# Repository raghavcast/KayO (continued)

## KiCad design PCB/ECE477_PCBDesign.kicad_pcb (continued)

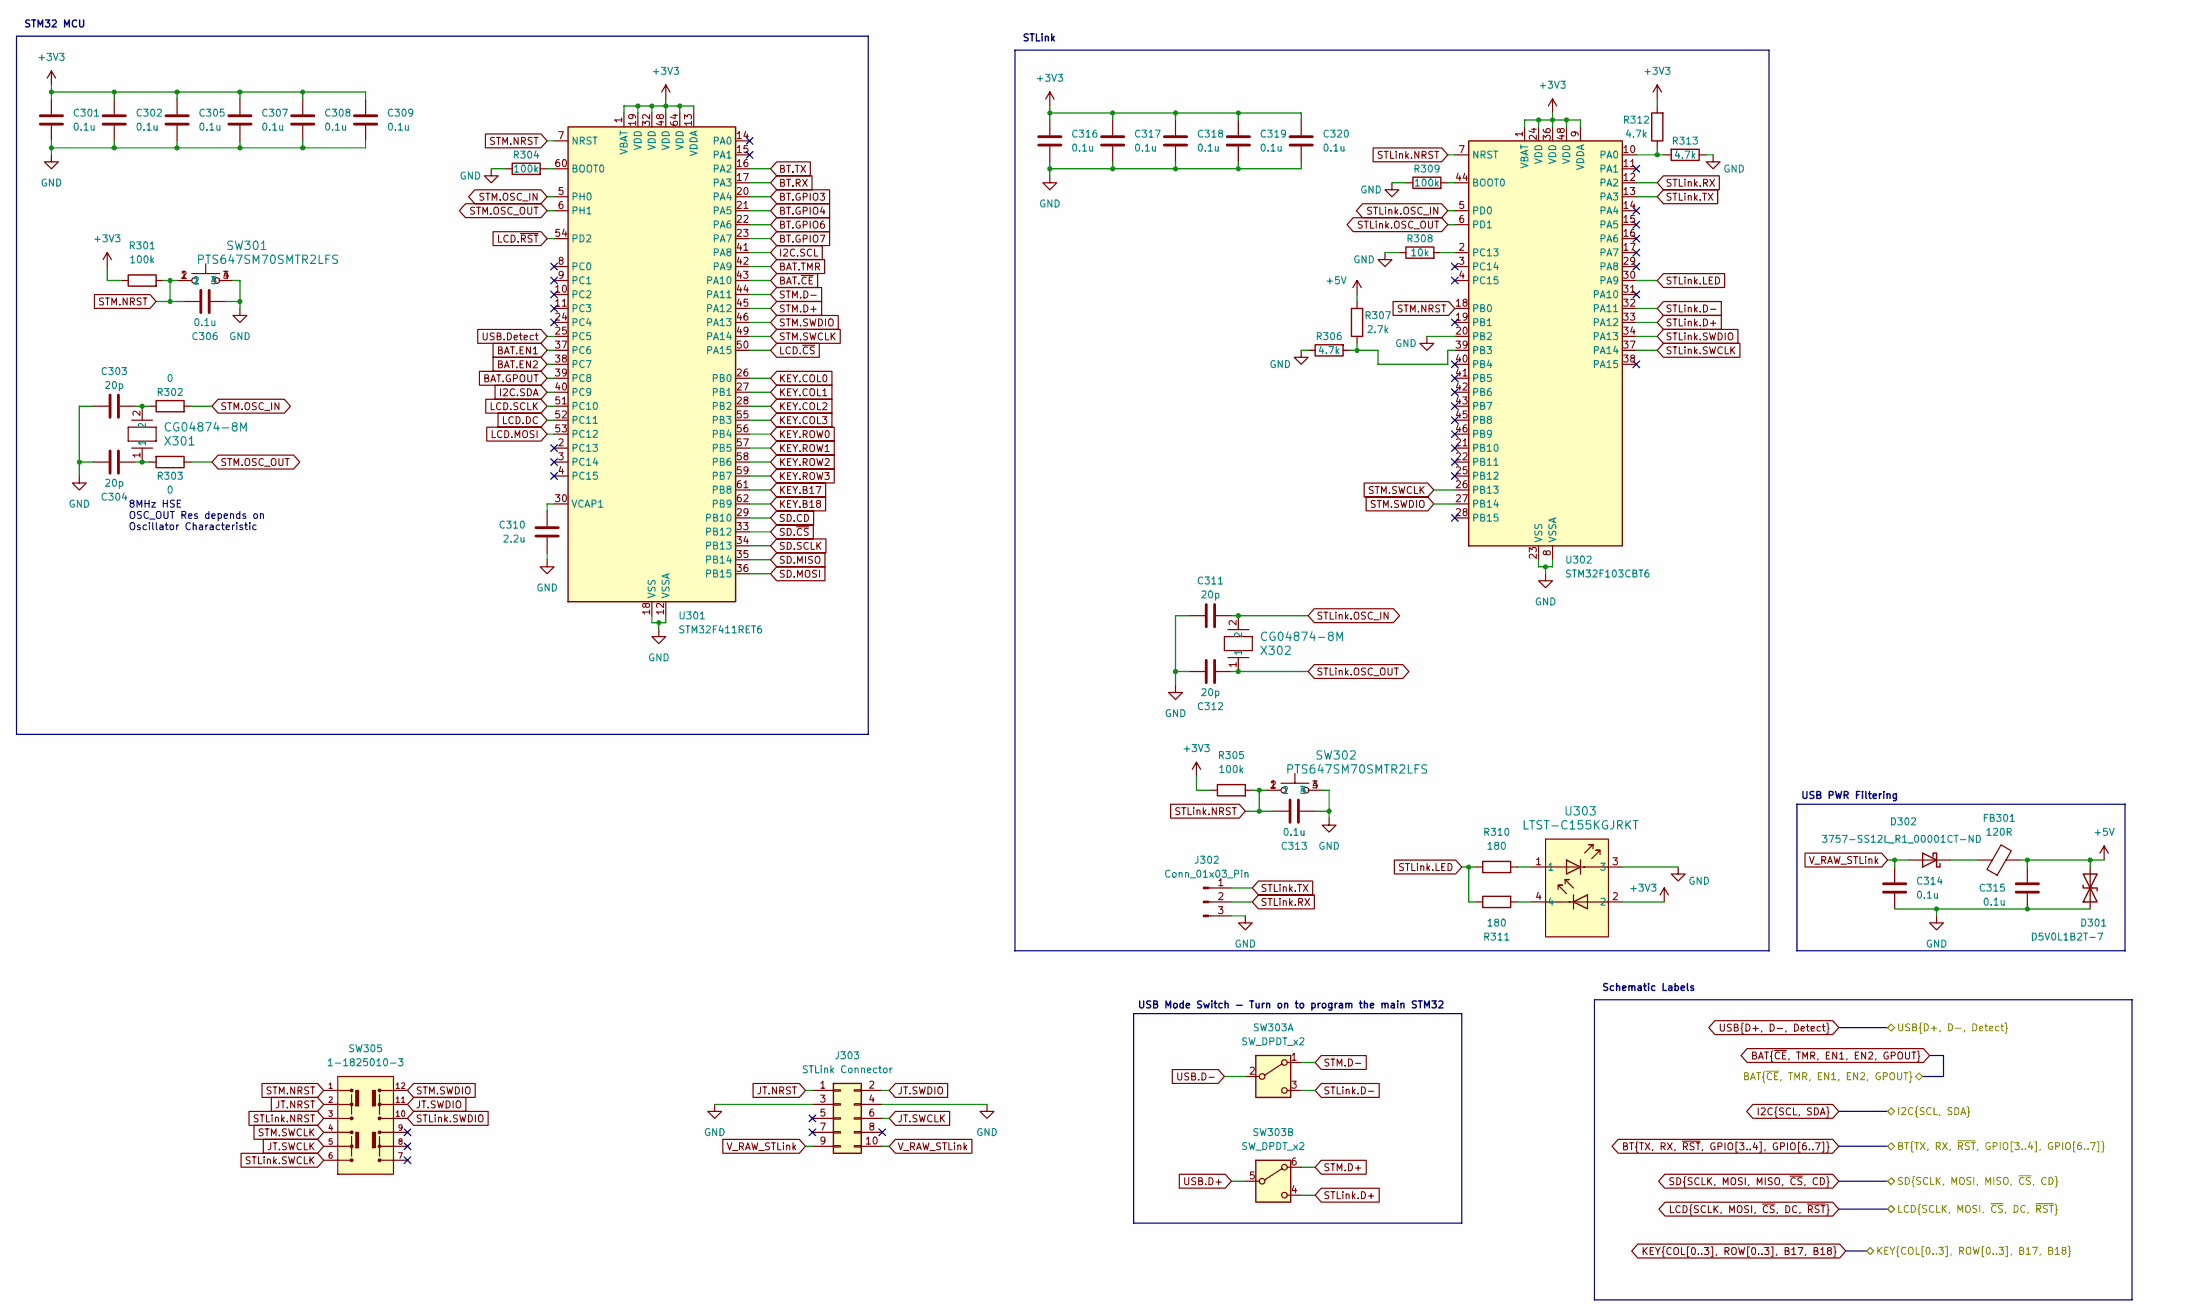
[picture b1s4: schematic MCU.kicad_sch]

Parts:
C301, C302, C305, C306, C307, C308, C309, C313, C316, C317, C318, C319, C320: 0.1u; C_0603_1608Metric_Pad1.08x0.95mm_HandSolder; Mfg. Part # GRM033R61A104ME15D; DigiKey Part 490-5405-1-ND
C303, C304, C311, C312: 20p; C_0603_1608Metric_Pad1.08x0.95mm_HandSolder; Mfg. Part # CC0603JRNPO9BN200; DigiKey Part 311-1424-1-ND
C310: 2.2u; C_0603_1608Metric_Pad1.08x0.95mm_HandSolder; Mfg. Part # GRM188R61E225KA12D; DigiKey Part 490-10731-1-ND
C314, C315: 0.1u; C_0603_1608Metric_Pad1.08x0.95mm_HandSolder; Mfg. Part # GRM033R61A104ME15D; LCSC C1525
D301: D5V0L1B2T-7; D_SOD-523; Mfg. Part # D5V0L1B2T-7; LCSC C508181
D302: 3757-SS12L_R1_00001CT-ND; D_SMA; Mfg. Part # SS12L_R1_00001; LCSC C36975
FB301: 120R; L_0603_1608Metric; Mfg. Part # BLM18BD121SH1D; LCSC C279682
J302: Conn_01x03_Pin; PinHeader_1x03_P2.54mm_Vertical
J303: STLink Connector; CONN10_302-S101_OST; Mfg. Part # 302-S101; DigiKey Part ED1543-ND
R301, R304, R305, R309: 100k; R_0603_1608Metric_Pad0.98x0.95mm_HandSolder; Mfg. Part # RC0603FR-07100KL; DigiKey Part 311-100KHRCT-ND
R302, R303: 0; R_0603_1608Metric_Pad0.98x0.95mm_HandSolder; Mfg. Part # RC0603JR-070RL; DigiKey Part 311-0.0GRCT-ND
R306, R312, R313: 4.7k; R_0603_1608Metric_Pad0.98x0.95mm_HandSolder; Mfg. Part # RC0603FR-074K7L; DigiKey Part 311-4.70KHRCT-ND
R307: 2.7k; R_0603_1608Metric_Pad0.98x0.95mm_HandSolder; Mfg. Part # RMCF0603FT2K70; DigiKey Part RMCF0603FT2K70CT-ND
R308: 10k; R_0603_1608Metric_Pad0.98x0.95mm_HandSolder; Mfg. Part # RC0603JR-0710KL; DigiKey Part 311-10KGRCT-ND
R310, R311: 180; R_0603_1608Metric_Pad0.98x0.95mm_HandSolder; Mfg. Part # RC0603FR-13180RL; DigiKey Part 13-RC0603FR-13180RLCT-ND
SW301, SW302: PTS647SM70SMTR2LFS; PTS647SM70SMTR2LFS_CNK; Mfg. Part # PTS 647 SM70 SMTR2 LFS; DigiKey Part PTS647SM70SMTR2LFSCT-ND
SW303: SW_DPDT_x2; SW_JS202011SCQN; Mfg. Part # JS202011SCQN; DigiKey Part 401-2002-1-ND
SW305: 1-1825010-3; SW_1-1825010-3; Mfg. Part # 1-1825010-3
U301: STM32F411RET6; LQFP-64_10x10mm_P0.5mm; Mfg. Part # STM32F411RET6; DigiKey Part 497-14909-ND
U302: STM32F103CBT6; LQFP-48_7x7mm_P0.5mm; Mfg. Part # STM32F103CBT6; DigiKey Part 497-6288-ND
U303: LTST-C155KGJRKT; SON4_LTST-C155KGJRKT_LTO; Mfg. Part # LTST-C155KGJRKT; DigiKey Part 160-1409-1-ND
X301, X302: CG04874-8M; XTAL_CG04874_NDK; Mfg. Part # CG04874-8M; DigiKey Part 644-CG04874-8MCT-ND

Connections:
+3V3: C301.1, C302.1, C305.1, C307.1, C308.1, C309.1, C316.1, C317.1, C318.1, C319.1, C320.1, R301.1, R305.1, R312.2, U301.1 (VBAT), U301.13 (VDDA), U301.19 (VDD), U301.32 (VDD), U301.48 (VDD), U301.64 (VDD), U302.1 (VBAT), U302.9 (VDDA), U302.24 (VDD), U302.36 (VDD), U302.48 (VDD), U303.2; also elsewhere on the board
+5V: C315.1, D301.2 (A2), FB301.2, R307.2; also elsewhere on the board
BAT.EN1: U301.37 (PC6); also elsewhere on the board
BAT.EN2: U301.38 (PC7); also elsewhere on the board
BAT.GPOUT: U301.39 (PC8); also elsewhere on the board
BAT.TMR: U301.42 (PA9); also elsewhere on the board
BAT.~CE: U301.43 (PA10); also elsewhere on the board
BT.GPIO3: U301.20 (PA4); also elsewhere on the board
BT.GPIO4: U301.21 (PA5); also elsewhere on the board
BT.GPIO6: U301.22 (PA6); also elsewhere on the board
BT.GPIO7: U301.23 (PA7); also elsewhere on the board
BT.RX: U301.17 (PA3); also elsewhere on the board
BT.TX: U301.16 (PA2); also elsewhere on the board
GND: C301.2, C302.2, C303.1, C304.1, C305.2, C306.1, C307.2, C308.2, C309.2, C310.2, C311.1, C312.1, C313.1, C314.2, C315.2, C316.2, C317.2, C318.2, C319.2, C320.2, D301.1 (A1), J302.3, J303.3, J303.4, R304.1, R306.1, R308.1, R309.1, R313.1, SW301.3, SW301.4, SW302.3, SW302.4, U301.12 (VSSA), U301.18 (VSS), U301.31 (VSS), U301.47 (VSS), U301.63 (VSS), U302.8 (VSSA), U302.20 (PB2), U302.23 (VSS), U302.35 (VSS), U302.47 (VSS), U303.3; also elsewhere on the board
I2C.SCL: U301.41 (PA8); also elsewhere on the board
I2C.SDA: U301.40 (PC9); also elsewhere on the board
JT.NRST: J303.1, SW305.2
JT.SWCLK: J303.6, SW305.5
JT.SWDIO: J303.2, SW305.11
KEY.B17: U301.61 (PB8); also elsewhere on the board
KEY.B18: U301.62 (PB9); also elsewhere on the board
KEY.COL0: U301.26 (PB0); also elsewhere on the board
KEY.COL1: U301.27 (PB1); also elsewhere on the board
KEY.COL2: U301.28 (PB2); also elsewhere on the board
KEY.COL3: U301.55 (PB3); also elsewhere on the board
KEY.ROW0: U301.56 (PB4); also elsewhere on the board
KEY.ROW1: U301.57 (PB5); also elsewhere on the board
KEY.ROW2: U301.58 (PB6); also elsewhere on the board
KEY.ROW3: U301.59 (PB7); also elsewhere on the board
LCD.DC: U301.52 (PC11); also elsewhere on the board
LCD.MOSI: U301.53 (PC12); also elsewhere on the board
LCD.SCLK: U301.51 (PC10); also elsewhere on the board
LCD.~CS: U301.50 (PA15); also elsewhere on the board
LCD.~RST: U301.54 (PD2); also elsewhere on the board
unnamed: C303.2, R302.1, X301.2
unnamed: C304.2, R303.2, X301.1
unnamed: D302.1 (K), FB301.1
unnamed: R310.2, U303.1
unnamed: R311.2, U303.4
unnamed: R304.2, U301.60 (BOOT0)
unnamed: C310.1, U301.30 (VCAP1)
unnamed: R309.2, U302.44 (BOOT0)
unnamed: R312.1, R313.2, U302.10 (PA0)
unnamed: R306.2, R307.1, U302.39 (PB3)
unnamed: R308.2, U302.2 (PC13)
SD.CD: U301.29 (PB10); also elsewhere on the board
SD.MISO: U301.35 (PB14); also elsewhere on the board
SD.MOSI: U301.36 (PB15); also elsewhere on the board
SD.SCLK: U301.34 (PB13); also elsewhere on the board
SD.~CS: U301.33 (PB12); also elsewhere on the board
STLink.D+: SW303.4 (C), U302.33 (PA12)
STLink.D-: SW303.3 (C), U302.32 (PA11)
STLink.LED: R310.1, R311.1, U302.30 (PA9)
STLink.NRST: C313.2, R305.2, SW302.1, SW302.2, SW305.3, U302.7 (NRST)
STLink.OSC_IN: C311.2, U302.5 (PD0), X302.2
STLink.OSC_OUT: C312.2, U302.6 (PD1), X302.1
STLink.RX: J302.2, U302.12 (PA2)
STLink.SWCLK: SW305.6, U302.37 (PA14)
STLink.SWDIO: SW305.10, U302.34 (PA13)
STLink.TX: J302.1, U302.13 (PA3)
STM.D+: SW303.6 (A), U301.45 (PA12)
STM.D-: SW303.1 (A), U301.44 (PA11)
STM.NRST: C306.2, R301.2, SW301.1, SW301.2, SW305.1, U301.7 (NRST), U302.18 (PB0)
STM.OSC_IN: R302.2, U301.5 (PH0)
STM.OSC_OUT: R303.1, U301.6 (PH1)
STM.SWCLK: SW305.4, U301.49 (PA14), U302.26 (PB13)
STM.SWDIO: SW305.12, U301.46 (PA13), U302.27 (PB14)
USB.D+: SW303.5 (B); also elsewhere on the board
USB.D-: SW303.2 (B); also elsewhere on the board
USB.Detect: U301.25 (PC5); also elsewhere on the board
V_RAW_STLink: C314.1, D302.2 (A), J303.9, J303.10

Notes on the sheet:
STM32 MCU
Schematic Labels
STLink
USB Mode Switch - Turn on to program the main STM32
8MHz HSE OSC_OUT Res depends on Oscillator Characteristic
USB PWR Filtering

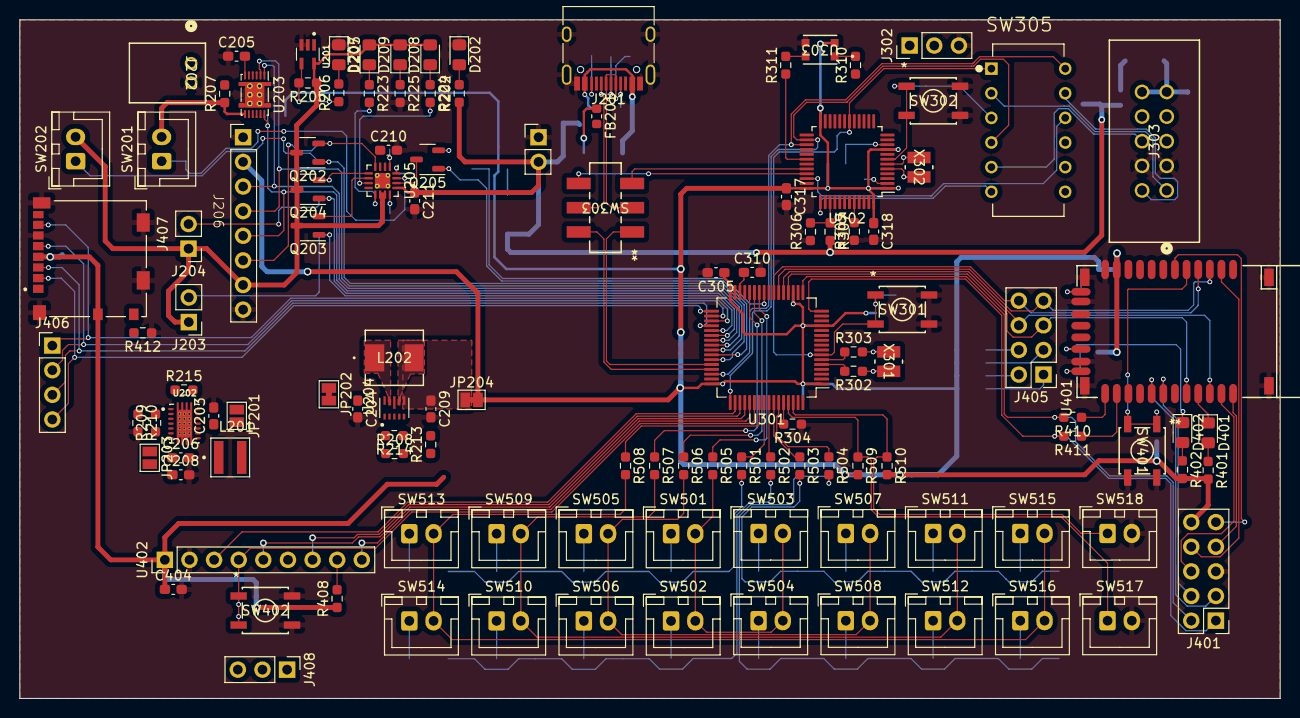
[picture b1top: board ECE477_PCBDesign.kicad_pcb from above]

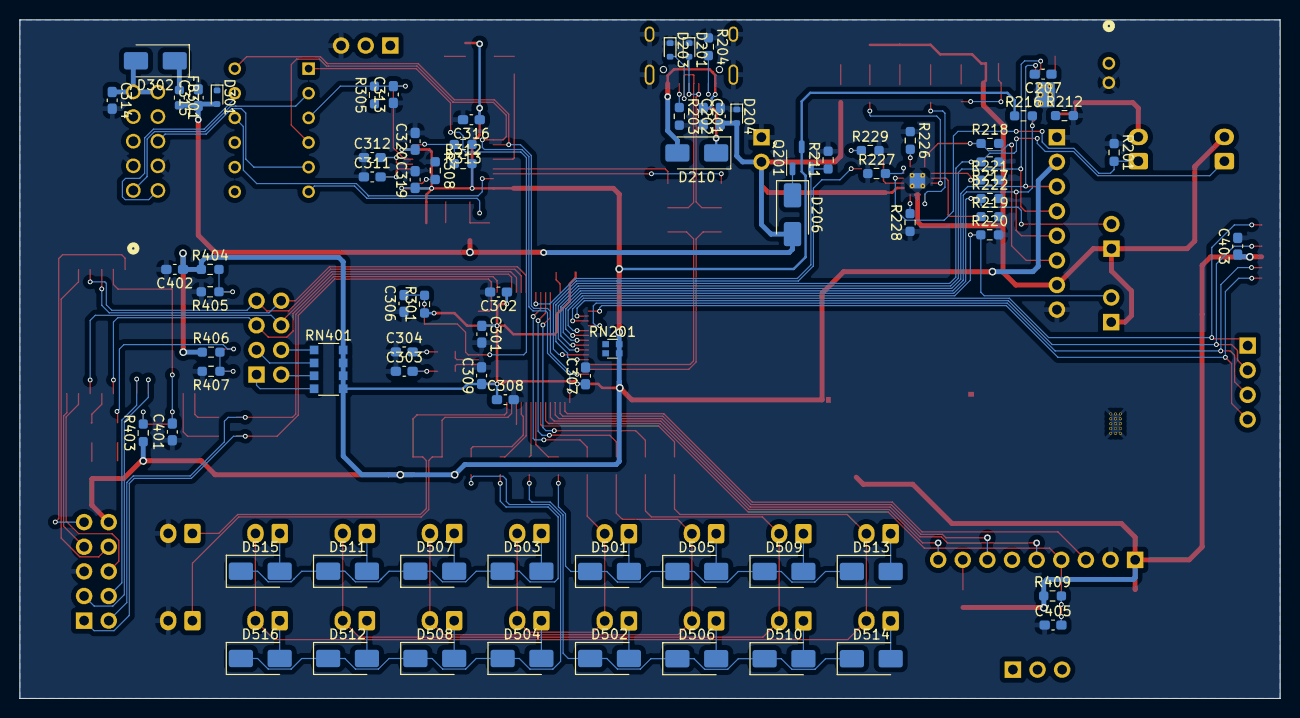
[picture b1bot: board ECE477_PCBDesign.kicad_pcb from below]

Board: 2 copper layers, 130.0 x 70.0 mm, 195 parts (77 on the bottom side), 154 nets.

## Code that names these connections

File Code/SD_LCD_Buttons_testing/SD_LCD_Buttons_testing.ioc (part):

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Mcu.Name=STM32F411R(C-E)Tx
Mcu.Package=LQFP64
Mcu.UserName=STM32F411RETx
PA1.GPIOParameters=GPIO_Label
PA1.GPIO_Label=Debug_LED
PA1.Signal=GPIO_Output
PA10.Mode=Asynchronous
PA10.Signal=USART1_RX
PA11.GPIOParameters=GPIO_Label
PA11.GPIO_Label=USB_DM
PA11.Mode=Device_Only
PA11.Signal=USB_OTG_FS_DM
PA12.GPIOParameters=GPIO_Label
PA12.GPIO_Label=USB_DP
PA12.Mode=Device_Only
PA12.Signal=USB_OTG_FS_DP
PA13.GPIOParameters=GPIO_Label
PA13.GPIO_Label=SWDIO
PA13.Mode=Serial_Wire
PA13.Signal=SYS_JTMS-SWDIO
PA14.GPIOParameters=GPIO_Label
PA14.GPIO_Label=SWCLK
PA14.Mode=Serial_Wire
PA14.Signal=SYS_JTCK-SWCLK
PA15.GPIOParameters=GPIO_Label
PA15.GPIO_Label=LCD_CS
PA15.Signal=GPIO_Output
PA2.GPIOParameters=GPIO_Label
PA2.GPIO_Label=USART_TX
PA2.Mode=Asynchronous
PA2.Signal=USART2_TX
PA3.GPIOParameters=GPIO_Label
PA3.GPIO_Label=USART_RX
PA3.Mode=Asynchronous
PA3.Signal=USART2_RX
PA6.GPIOParameters=GPIO_PuPd,GPIO_Label,GPIO_ModeDefaultOutputPP
PA6.GPIO_Label=BT_EN
PA6.GPIO_ModeDefaultOutputPP=GPIO_MODE_OUTPUT_OD
PA6.GPIO_PuPd=GPIO_NOPULL
PA6.Signal=GPIO_Output
PA8.GPIOParameters=GPIO_Label
PA8.GPIO_Label=BAT_SCL
PA8.Mode=I2C
PA8.Signal=I2C3_SCL
PA9.Mode=Asynchronous
PA9.Signal=USART1_TX
PB0.GPIOParameters=GPIO_Label
PB0.GPIO_Label=Col0
PB0.Signal=GPIO_Output
PB1.GPIOParameters=GPIO_Label
PB1.GPIO_Label=Col1
PB1.Signal=GPIO_Output
PB10.GPIOParameters=GPIO_PuPd,GPIO_Label
PB10.GPIO_Label=SD_Detect
PB10.GPIO_PuPd=GPIO_PULLUP
PB10.Signal=GPIO_Input
PB12.GPIOParameters=GPIO_PuPd,GPIO_Label
PB12.GPIO_Label=SD_CS
PB12.GPIO_PuPd=GPIO_PULLUP
PB12.Signal=GPIO_Output
PB13.GPIOParameters=GPIO_Label
PB13.GPIO_Label=SD_SCK
PB13.Mode=Full_Duplex_Master
PB13.Signal=SPI2_SCK
PB14.GPIOParameters=GPIO_PuPd,GPIO_Label
PB14.GPIO_Label=SD_MISO
PB14.GPIO_PuPd=GPIO_PULLUP
PB14.Mode=Full_Duplex_Master
PB14.Signal=SPI2_MISO
PB15.GPIOParameters=GPIO_PuPd,GPIO_Label
PB15.GPIO_Label=SD_MOSI
PB15.GPIO_PuPd=GPIO_PULLUP
PB15.Mode=Full_Duplex_Master
PB15.Signal=SPI2_MOSI
PB2.GPIOParameters=GPIO_Label
PB2.GPIO_Label=Col2
PB2.Signal=GPIO_Output
PB3.GPIOParameters=GPIO_Label
PB3.GPIO_Label=Col3
PB3.Signal=GPIO_Output
PB4.GPIOParameters=GPIO_PuPd,GPIO_Label
PB4.GPIO_Label=Row0
PB4.GPIO_PuPd=GPIO_PULLDOWN
PB4.Signal=GPIO_Input
PB5.GPIOParameters=GPIO_PuPd,GPIO_Label
PB5.GPIO_Label=Row1
PB5.GPIO_PuPd=GPIO_PULLDOWN
PB5.Signal=GPIO_Input
PB6.GPIOParameters=GPIO_PuPd,GPIO_Label
PB6.GPIO_Label=Row2
PB6.GPIO_PuPd=GPIO_PULLDOWN
PB6.Signal=GPIO_Input
PB7.GPIOParameters=GPIO_PuPd,GPIO_Label
PB7.GPIO_Label=Row3
PB7.GPIO_PuPd=GPIO_PULLDOWN
PB7.Signal=GPIO_Input
PB8.GPIOParameters=GPIO_PuPd,GPIO_Label
PB8.GPIO_Label=Button17
PB8.GPIO_PuPd=GPIO_PULLDOWN
PB8.Signal=GPIO_Input
PB9.GPIOParameters=GPIO_PuPd,GPIO_Label
PB9.GPIO_Label=Button18
PB9.GPIO_PuPd=GPIO_PULLDOWN
PB9.Signal=GPIO_Input
PC10.GPIOParameters=GPIO_Label
PC10.GPIO_Label=LCD_SCK
PC10.Mode=TX_Only_Simplex_Unidirect_Master
PC10.Signal=SPI3_SCK
PC11.GPIOParameters=GPIO_Label
PC11.GPIO_Label=LCD_DC
PC11.Signal=GPIO_Output
PC12.GPIOParameters=GPIO_Label
PC12.GPIO_Label=LCD_MOSI
PC12.Mode=TX_Only_Simplex_Unidirect_Master
PC12.Signal=SPI3_MOSI
PC13-ANTI_TAMP.GPIOParameters=GPIO_Label
PC13-ANTI_TAMP.GPIO_Label=New_Button18
PC13-ANTI_TAMP.Signal=GPIO_Input
PC5.GPIOParameters=GPIO_Label,GPIO_ModeDefaultEXTI
PC5.GPIO_Label=USB_Detect
PC5.GPIO_ModeDefaultEXTI=GPIO_MODE_IT_RISING_FALLING
PC5.Signal=GPXTI5
PC7.GPIOParameters=GPIO_Label
PC7.GPIO_Label=BAT_CE
PC7.Signal=GPIO_Output
PC8.GPIOParameters=GPIO_Label
PC8.GPIO_Label=BAT_GPOUT
PC8.Signal=GPXTI8
PC9.GPIOParameters=GPIO_Label
PC9.GPIO_Label=BAT_SDA
PC9.Mode=I2C
PC9.Signal=I2C3_SDA
PD2.GPIOParameters=GPIO_Label
PD2.GPIO_Label=LCD_Reset
PD2.Signal=GPIO_Output
PH0\ -\ OSC_IN.Mode=HSE-External-Clock-Source
PH0\ -\ OSC_IN.Signal=RCC_OSC_IN
PH1\ -\ OSC_OUT.Mode=HSE-External-Clock-Source
PH1\ -\ OSC_OUT.Signal=RCC_OSC_OUT
RCC.HSE_VALUE=8000000
RCC.SYSCLKFreq_VALUE=96000000
RCC.SYSCLKSource=RCC_SYSCLKSOURCE_PLLCLK
board=NUCLEO-F411RE
boardIOC=true

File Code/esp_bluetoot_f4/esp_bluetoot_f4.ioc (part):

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Mcu.Name=STM32F411R(C-E)Tx
Mcu.Package=LQFP64
Mcu.UserName=STM32F411RETx
PA10.GPIOParameters=GPIO_Label
PA10.GPIO_Label=BT_RX
PA10.Mode=Asynchronous
PA10.Signal=USART1_RX
PA13.GPIOParameters=GPIO_Label
PA13.GPIO_Label=TMS
PA13.Mode=Serial_Wire
PA13.Signal=SYS_JTMS-SWDIO
PA14.GPIOParameters=GPIO_Label
PA14.GPIO_Label=TCK
PA14.Mode=Serial_Wire
PA14.Signal=SYS_JTCK-SWCLK
PA2.GPIOParameters=GPIO_Label
PA2.GPIO_Label=USART_TX
PA2.Mode=Asynchronous
PA2.Signal=USART2_TX
PA3.GPIOParameters=GPIO_Label
PA3.GPIO_Label=USART_RX
PA3.Mode=Asynchronous
PA3.Signal=USART2_RX
PA5.GPIOParameters=GPIO_Label
PA5.GPIO_Label=LD2 [Green Led]
PA5.Signal=GPIO_Output
PA9.GPIOParameters=GPIO_Label
PA9.GPIO_Label=BT_TX
PA9.Mode=Asynchronous
PA9.Signal=USART1_TX
PB0.GPIOParameters=GPIO_PuPd,GPIO_Label,GPIO_ModeDefaultOutputPP
PB0.GPIO_Label=Col0
PB0.GPIO_ModeDefaultOutputPP=GPIO_MODE_OUTPUT_OD
PB0.GPIO_PuPd=GPIO_NOPULL
PB0.Signal=GPIO_Output
PB1.GPIOParameters=GPIO_PuPd,GPIO_Label,GPIO_ModeDefaultOutputPP
PB1.GPIO_Label=Col1
PB1.GPIO_ModeDefaultOutputPP=GPIO_MODE_OUTPUT_OD
PB1.GPIO_PuPd=GPIO_NOPULL
PB1.Signal=GPIO_Output
PB2.GPIOParameters=GPIO_PuPd,GPIO_Label,GPIO_ModeDefaultOutputPP
PB2.GPIO_Label=Col2
PB2.GPIO_ModeDefaultOutputPP=GPIO_MODE_OUTPUT_OD
PB2.GPIO_PuPd=GPIO_NOPULL
PB2.Signal=GPIO_Output
PB3.GPIOParameters=GPIO_PuPd,GPIO_Label,GPIO_ModeDefaultOutputPP
PB3.GPIO_Label=Col3
PB3.GPIO_ModeDefaultOutputPP=GPIO_MODE_OUTPUT_OD
PB3.GPIO_PuPd=GPIO_NOPULL
PB3.Signal=GPIO_Output
PB4.GPIOParameters=GPIO_PuPd,GPIO_Label
PB4.GPIO_Label=Row0
PB4.GPIO_PuPd=GPIO_PULLUP
PB4.Signal=GPIO_Input
PB5.GPIOParameters=GPIO_PuPd,GPIO_Label
PB5.GPIO_Label=Row1
PB5.GPIO_PuPd=GPIO_PULLUP
PB5.Signal=GPIO_Input
PB6.GPIOParameters=GPIO_PuPd,GPIO_Label
PB6.GPIO_Label=Row2
PB6.GPIO_PuPd=GPIO_PULLUP
PB6.Signal=GPIO_Input
PB7.GPIOParameters=GPIO_PuPd,GPIO_Label
PB7.GPIO_Label=Row3
PB7.GPIO_PuPd=GPIO_PULLUP
PB7.Signal=GPIO_Input
PB8.GPIOParameters=GPIO_PuPd,GPIO_Label
PB8.GPIO_Label=Button17
PB8.GPIO_PuPd=GPIO_PULLDOWN
PB8.Signal=GPIO_Input
PB9.GPIOParameters=GPIO_PuPd,GPIO_Label
PB9.GPIO_Label=Button18
PB9.GPIO_PuPd=GPIO_PULLDOWN
PB9.Signal=GPIO_Input
PC13-ANTI_TAMP.GPIOParameters=GPIO_Label,GPIO_ModeDefaultEXTI
PC13-ANTI_TAMP.GPIO_Label=B1 [Blue PushButton]
PC13-ANTI_TAMP.GPIO_ModeDefaultEXTI=GPIO_MODE_IT_FALLING
PC13-ANTI_TAMP.Signal=GPXTI13
PC14-OSC32_IN.Mode=LSE-External-Oscillator
PC14-OSC32_IN.Signal=RCC_OSC32_IN
PC15-OSC32_OUT.Mode=LSE-External-Oscillator
PC15-OSC32_OUT.Signal=RCC_OSC32_OUT
PC6.GPIOParameters=GPIO_Label
PC6.GPIO_Label=BT_EN
PC6.Signal=GPIO_Output
PH0\ -\ OSC_IN.Mode=HSE-External-Clock-Source
PH0\ -\ OSC_IN.Signal=RCC_OSC_IN
PH1\ -\ OSC_OUT.Mode=HSE-External-Clock-Source
PH1\ -\ OSC_OUT.Signal=RCC_OSC_OUT
RCC.HSE_VALUE=8000000
RCC.SYSCLKFreq_VALUE=96000000
RCC.SYSCLKSource=RCC_SYSCLKSOURCE_PLLCLK
board=NUCLEO-F411RE
boardIOC=true

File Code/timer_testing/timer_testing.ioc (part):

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Mcu.Name=STM32F042K(4-6)Tx
Mcu.Package=LQFP32
Mcu.UserName=STM32F042K6Tx
PA0.GPIOParameters=GPIO_PuPd,GPIO_Label,GPIO_ModeDefaultOutputPP
PA0.GPIO_Label=Col1
PA0.GPIO_ModeDefaultOutputPP=GPIO_MODE_OUTPUT_OD
PA0.GPIO_PuPd=GPIO_NOPULL
PA0.Signal=GPIO_Output
PA1.GPIOParameters=GPIO_PuPd,GPIO_Label,GPIO_ModeDefaultOutputPP
PA1.GPIO_Label=Col2
PA1.GPIO_ModeDefaultOutputPP=GPIO_MODE_OUTPUT_OD
PA1.GPIO_PuPd=GPIO_NOPULL
PA1.Signal=GPIO_Output
PA11.Mode=Device
PA11.Signal=USB_DM
PA12.Mode=Device
PA12.Signal=USB_DP
PA2.GPIOParameters=GPIO_PuPd,GPIO_Label,GPIO_ModeDefaultOutputPP
PA2.GPIO_Label=Col3
PA2.GPIO_ModeDefaultOutputPP=GPIO_MODE_OUTPUT_OD
PA2.GPIO_PuPd=GPIO_NOPULL
PA2.Signal=GPIO_Output
PA3.GPIOParameters=GPIO_PuPd,GPIO_Label,GPIO_ModeDefaultOutputPP
PA3.GPIO_Label=Col4
PA3.GPIO_ModeDefaultOutputPP=GPIO_MODE_OUTPUT_OD
PA3.GPIO_PuPd=GPIO_NOPULL
PA3.Signal=GPIO_Output
PA4.GPIOParameters=GPIO_PuPd,GPIO_Label
PA4.GPIO_Label=Row1
PA4.GPIO_PuPd=GPIO_PULLUP
PA4.Signal=GPIO_Input
PA5.GPIOParameters=GPIO_PuPd,GPIO_Label
PA5.GPIO_Label=Row2
PA5.GPIO_PuPd=GPIO_PULLUP
PA5.Signal=GPIO_Input
PA6.GPIOParameters=GPIO_PuPd,GPIO_Label
PA6.GPIO_Label=Row3
PA6.GPIO_PuPd=GPIO_PULLUP
PA6.Signal=GPIO_Input
PA7.GPIOParameters=GPIO_PuPd,GPIO_Label
PA7.GPIO_Label=Row4
PA7.GPIO_PuPd=GPIO_PULLUP
PA7.Signal=GPIO_Input
PB7.GPIOParameters=GPIO_PuPd,GPIO_Label
PB7.GPIO_Label=Button
PB7.GPIO_PuPd=GPIO_PULLDOWN
PB7.Signal=GPIO_Input
RCC.SYSCLKFreq_VALUE=48000000
RCC.SYSCLKSource=RCC_SYSCLKSOURCE_HSI48
board=custom

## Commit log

2024-01-14 Finished first button press
2024-01-17 Started timer testing
2024-01-17 Ran into flash size problems
2024-01-19 Finished timer interrupts - timer_testing_f4
2024-01-23 debounce v1
2024-01-24 Removed unnecessary files
2024-01-25 PCB init - Minh
2024-01-25 PCB update - Minh
2024-01-26 Revert "PCB Update - Minh"
    This reverts commit c90ea9d44a3cf4e98d0b0e6b660cc2839c15f6ce.
2024-01-26 Revert "PCB update - Minh"
    This reverts commit 0608947e49f54a64abc006b190e3b029bac40ad1.
2024-01-26 Revert "Revert "PCB update - Minh""
    This reverts commit c5ab976102d31394b601432f6e18493af52002e1.
2024-01-26 Revert "Revert "PCB Update - Minh""
    This reverts commit a71bc01ae53ec754d7dc3d2935acb74adc996996.
2024-02-03 Finished LCD-SD interface testing code
2024-02-08 Update 90% done
2024-02-12 Finished integration of SD, LCD and buttons
2024-02-14 battbaby is alive
2024-02-15 added comments for battbaby
2024-02-15 added gitignore
2024-02-15 Stuff
2024-02-17 design 02/17
2024-02-19 Uploading Bluetoth running idea
2024-02-21 Update Rev 2
2024-02-21 Update v2 with Stitching
2024-02-23 Almost finished
2024-02-26 Wrote bluetooth integration for esp32
2024-02-27 Redesign bluetooth of v2
2024-03-02 Finished bt code 4byte
2024-03-04 Update PCB Design v2
2024-03-05 Complete Version 2
2024-03-05 Finished prototype. Need to write esp tx
2024-03-28 PCB Update
2024-04-13 Finished final product
2024-04-13 Started hitbox code
2024-04-13 Added images and PCB
2024-04-13 Removed metadata
2024-04-13 Finished hitbox code
2024-04-13 updated PCB
